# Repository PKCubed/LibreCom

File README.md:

# LibreCom
**An Open-Source, Long-Range, Sub-GHz Digital Intercom System**

Welcome to the **LibreCom** repository. This project aims to build a fully open-source, digital wireless intercom system designed for live event production, theater crews, and other communication applications.

By combining the wall-penetrating power of **Sub-GHz radio**, high quality low bandwidth **OPUS audio compression**, and a custom **TDMA (Time-Division Multiple Access)** protocol, this system supports multiple simultaneous talkers and infinite listeners over distances that standard 2.4GHz/Wi-Fi systems cannot reach.

This project wont be quite as feature rich as the top-of-the-line communication systems on the market, but with it's incredibly low price and open-source nature, we hope for it to reach into the live event production world.

## Sponsored by PCBWay!

<p align="center">
  
</p>

A huge thank you to **[PCBWay](https://www.pcbway.com/)** for sponsoring LibreCom!

PCBWay is providing PCB fabrication and assembly for our prototype hardware. Hardware projects like this one need many board revisions to get RF layout, audio grounding, and power design right. Their support lets us iterate quickly without the cost of each spin slowing development down.

We're currently just about to order our first PCB revision, and once we get it back we'll upload pictures and share our experience here.

If you're building your own LibreCom hardware, the Gerber files in the production folders are ready to upload directly to PCBWay. They also offer **PCB assembly**, **stencils**, **3D printing**, and **CNC machining**, which are useful if you want a finished enclosure for your belt pack too.

**[Order LibreCom boards from PCBWay](https://www.pcbway.com/)**

---

## System Feature Goals

### Overall System
* **Low Latency:** Latency should be low enough such that conversations can be made quickly.
* **Flexibility:** Each belt pack should support any standard TRRS headset. The hub should allow analog connections as well to interface with other systems.

### The Belt Packs (End-User Nodes)
The belt packs are designed to be cheap, rugged, and feature-rich for live-event professionals.
* **Standard Headset Support:** Uses universal TRRS (3.5mm) headsets (CTIA).
* **Local IEM Mixing:** Features an external stereo input jack. You can plug in an In-Ear Monitor (IEM) pack or other device, and the belt pack will mix this audio locally with the coms feed fed into the headset.
* **Spatial Panning:** Comm audio can be software-panned entirely to the Left or Right ear, allowing users to separate crew chatter from program audio.
* **Audio Ducking** User's can configure the belt packs to duck other audio making way for priority talkers.
* **Physical Controls:**
  * Volume Knob
  * Push-To-Talk (PTT) Button
  * Push-To-Mute Button (Configurable to mute either the mic, the comm feed, or the local IEM feed)
* **VOX Support:** Voice Operated Exchange for hands-free operation without needing the PTT button.
* **Multiple Talk Groups:** More than one conversation space for separating teams like video and stage crews while keeping the ability to broadcast to specific or all talk groups.

### The Base Station (Central Matrix)
For structured events (theater, concerts), the system relies on a Base Station to act as the TDMA master clock and audio routing matrix.
* **Program Audio Injection:** Jacks to input external audio (like a Front-of-House stage mix) to be broadcast to all belt packs.
* **Hardware Outputs:** Multiple physical audio outputs on the base station that can be routed in software (e.g., routing "Talk Group A" to Output 1, and "Talk Group B" to Output 2 for the stage manager's console).
* **Web UI Management:** The base station hosts a local web server interface. Stage managers can connect via phone/laptop to change user volumes, assign talk groups, configure priorities, and monitor battery levels.

### Decentralized "Mesh" Mode (stretch goal)
No base station? No problem. The belt packs can be configured to operate in a completely decentralized mode. Perfect for outdoor sports (skiing, hiking, airsoft) where a group of friends can communicate directly point-to-point like highly advanced digital walkie-talkies.

---

## Hardware Architecture

The hardware is designed to decouple the heavy digital signal processing from the strict timing requirements of the radio link.

* **Belt Pack Main Processor (MCU):** ESP32-S3
* **Radio Transceiver:** SX1262
* **Audio Frontend:** I2S Audio DAC and ADC IC with amplification for both headphones and for a microphone.
* **The Hub:** Raspberry Pi Hat with custom hat including SX1262, I2S ADCs and DACs for physical audio IO, and some kind of physical user interface for quick adjustments to the system's configuration

---

## Licensing

To ensure this project remains open and beneficial to the community while allowing for commercial manufacturing:

* **Software / Firmware:** Licensed under the **GNU GPLv3**.
* **Hardware / PCBs:** Licensed under the **CERN-OHL-S** (Strongly Reciprocal). 

You are free to build, use, and sell this hardware. However, if you modify the circuit board designs or the firmware and distribute the resulting product, you must share your modifications back with the community under the same open licenses.

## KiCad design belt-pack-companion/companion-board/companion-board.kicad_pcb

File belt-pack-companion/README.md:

# ESP32 Pin Connections
| ESP32 Pin | Connection | | ESP32 Pin | Connection |
| --- | --- |-| --- | --- |
| 7 |  | | 19 | Button 1 |
| 6 | I2C SCL | | 20 | Button 2 |
| 5 | I2C SDA | | 21 |  |
| 4 | I2S SPK Data | | 26 |  |
| 3 |  | | 48 | SD DAT3 |
| 2 | I2S WCLK | | 47 | SD DAT2 |
| 1 |  | | 33 | CODEC Reset |
| 38 | I2S BCLK | | 34 | I2S MIC Data |
| 39 | SD CLK | | 35 |  |
| 40 | SD CMD  | | 36 |  |
| 41 | SD DAT0 | | 0 |  |
| 42 | SD DAT1 | |  |  |
| 45 | Red LED | | 43 |  |
| 46 | Green LED | | 44 |  |
| 37 |  | |  |  |

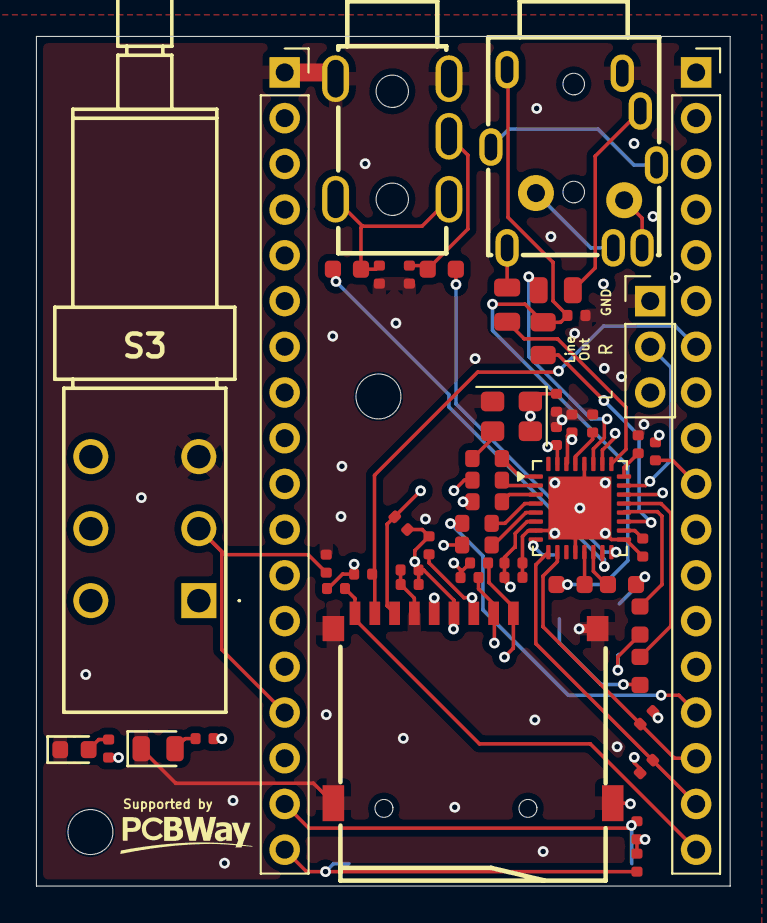
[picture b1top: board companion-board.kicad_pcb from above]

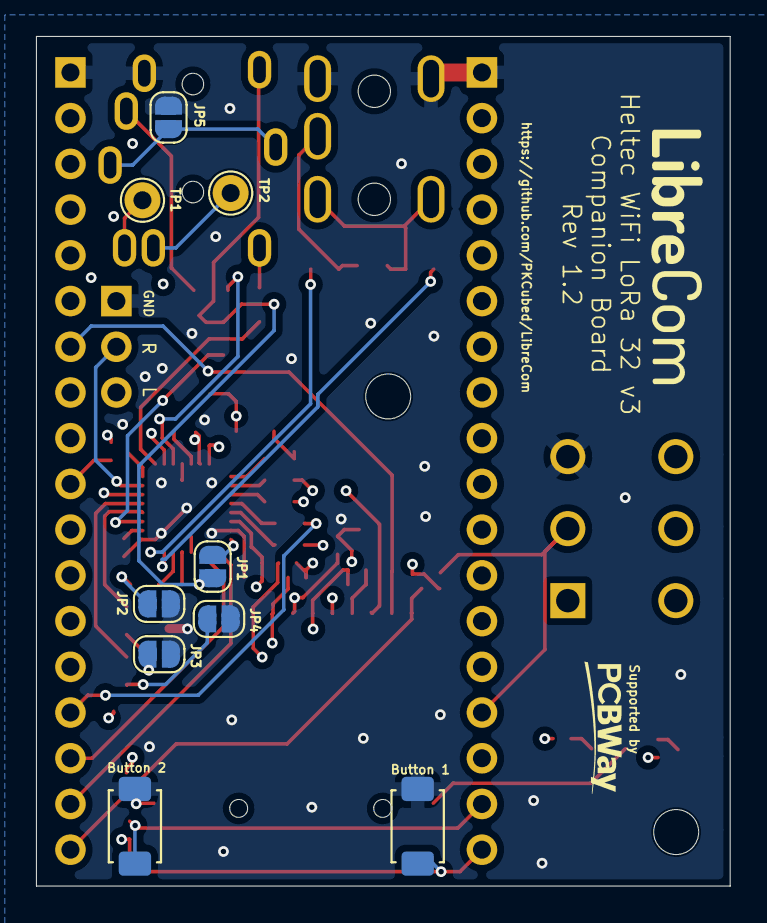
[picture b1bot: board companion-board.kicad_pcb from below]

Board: 4 copper layers, 38.5 x 47.2 mm, 63 parts (9 on the bottom side), 56 nets.

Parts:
C1, C4, C8, C9, C16: 10uF; C_0402
C2: 1uF; C_0402
C3: 1nF; C_0402
C5, C6: 47uF; C_0805
C7, C10, C11, C12, C13, C14: 100nF; C_0603
C15, C17: 100nF; C_0402
CARD1: TF-SMD_TF-01A
D1: Red; D_0603
D4: Green; D_0805
H1, H2: MountingHole; MountingHole_2.5mm
J1, J2: Conn_01x18_Socket; PinSocket_1x18_P2.54mm_Vertical
J3: AUDIO-TH_PJ313D
J4: Conn_01x03_Pin; PinHeader_1x03_P2.54mm_Vertical
JP1, JP2, JP3, JP4, JP5: SolderJumper_2_Open; SolderJumper-2_P1.3mm_Open_RoundedPad1.0x1.5mm
R1, R2, R3, R4: 27Ω; R_0603
R5: 10Ω; R_0603
R6: 2.7kΩ; R_0805
R7, R14: 4.7kΩ; R_0402
R8: 33Ω; R_0402
R9: 330Ω; R_0402
R13, R15, R16, R23, R24, R27, R28, R29, R30, R31: 10kΩ; R_0402
R18: 470Ω; R_0402
R26, R32, R33: 100kΩ; R_0402
S1, S2: Tactile Button, 160gf; SW_TS-1088-AR02016
S3: MPBS-22H01-F14; MPBS22H01F14
TP1, TP2: TestPoint; TestPoint_THTPad_D2.0mm_Drill1.0mm
U1: TLV320AIC3204; VQFN-32-1EP_5x5mm_P0.5mm_EP3.5x3.5mm
U2: AUDIO-TH_PJ-3401
X1: YC24.576MUBCE2O; Oscillator_SMD_Abracon_ASE-4Pin_3.2x2.5mm

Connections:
+3.3V: C1.1, C2.1, C3.1, C15.1, C16.1, C17.1, CARD1.4 (VDD), J1.2, J1.3, R7.2, R14.1, R15.2, R16.2, R23.1, R27.1, R28.1, R29.1, R30.1, R31.1, S3.1 (NO_1), U1.6 (IOVDD), U1.26 (LDOIN/HPVDD), U1.30 (LDO_SELECT), X1.1 (EN), X1.4 (Vdd)
Button_1: J2.18, R15.1, S2.1 (A)
Button_2: J2.17, R16.1, S1.1 (A)
Button_PTT: J2.15, R24.1, S3.2 (COM_1)
CODEC_RESET: J2.12, R13.2, U1.31 (~RESET)
GND: C1.2, C2.2, C3.2, C4.2, C8.2, C9.2, C15.2, C16.2, C17.2, CARD1.6 (VSS), CARD1.10 (GND), CARD1.11 (GND), CARD1.12 (GND), CARD1.13 (GND), D1.1, D4.1, J1.1, J2.1, J3.2, J4.1, JP2.2 (B), JP3.2 (B), JP4.2 (B), JP5.1 (A), R13.1, R24.2, R26.2, R32.2, R33.2, S1.2 (B), S2.2 (B), S3.3 (NC_1), U1.7 (IOVSS), U1.12 (SPI_SELECT), U1.17 (AVSS), U1.28 (DVSS), U1.33 (EP), U2.1 (GND/MIC), X1.2 (GND)
HS_Left: C5.2, U2.3 (L)
HS_Right: C6.2, U2.2 (R)
I^{2}C_SCL: J1.17, R7.1, U1.9 (SCL/~SS)
I^{2}C_SDA: J1.16, R14.2, U1.10 (SDA/MOSI)
I^{2}S_BCLK: J1.11, R4.1
I^{2}S_MCLK: R5.2, U1.1 (MCLK)
I^{2}S_MIC_DATA: J2.11, R2.1
I^{2}S_SPK_DATA: J1.15, R1.1
I^{2}S_WCLK: J1.13, R3.1
LED_Green: J1.5, R9.1
LED_Red: J1.6, R18.1
LINE_IN_L: C10.2, J3.4, R32.1
LINE_IN_R: C11.2, J3.3, R33.1
Line_Out_Left: J4.3, U1.22 (LOL)
Line_Out_Right: J4.2, U1.23 (LOR)
MIC: C7.2, JP1.1 (A), R6.2, R26.1, U2.4 (GND/MIC)
unnamed: D1.2, R18.2
unnamed: D4.2, R9.2
unnamed: J1.10, R8.2
unnamed: JP1.2 (B), U1.8 (SCLK/MFP3)
unnamed: C12.2, JP2.1 (A)
unnamed: C13.2, JP3.1 (A)
unnamed: C14.2, JP4.1 (A)
unnamed: JP5.2 (B), U2.7 (SHELL), U2.8 (SHELL)
unnamed: TP1.1 (1_1), U2.6
unnamed: TP2.1 (1_1), U2.5
unnamed: C8.1, U1.24 (AVDD)
unnamed: R3.2, U1.2 (BCLK)
unnamed: R1.2, U1.4 (DIN/MFP1)
unnamed: R2.2, U1.5 (DOUT/MFP2)
unnamed: C9.1, U1.29 (DVDD)
unnamed: C5.1, U1.25 (HPL)
unnamed: C6.1, U1.27 (HPR)
unnamed: C7.1, U1.13 (IN1_L)
unnamed: C12.1, U1.14 (IN1_R)
unnamed: C10.1, U1.15 (IN2_L)
unnamed: C11.1, U1.16 (IN2_R)
unnamed: C13.1, U1.20 (IN3_L)
unnamed: C14.1, U1.21 (IN3_R)
unnamed: R6.1, U1.19 (MICBIAS)
unnamed: C4.1, U1.18 (REF)
unnamed: R4.2, U1.3 (WCLK)
unnamed: R5.1, X1.3 (OUT)
SD_CLK: CARD1.5 (CLK(SCLK)), R8.1
SD_CMD: CARD1.3 (CMD(DI)), J1.9, R30.2
SD_DAT0: CARD1.7 (DAT0(D0)), J1.8, R29.2
SD_DAT1: CARD1.8 (DAT1(RSV)), J1.7, R28.2
SD_DAT2: CARD1.1 (DAT2(RSV)), J2.13, R27.2
SD_DAT3: CARD1.2 (CDDAT3(CS)), J2.14, R31.2
SD_DETECT: CARD1.9 (CD), J1.18, R23.2

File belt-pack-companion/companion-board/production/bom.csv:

Designator,Footprint,Quantity,Value,LCSC Part #
"C1, C16, C4, C8, C9",C_0402,5,10uF,C15525
"C10, C11, C12, C13, C14, C7",C_0603,6,100nF,C14663
"C15, C17",C_0402,2,100nF,C1525
C2,C_0402,1,1uF,C52923
C3,C_0402,1,1nF,C1523
"C5, C6",C_0805,2,47uF,C16780
CARD1,TF-SMD_TF-01A,1,~,C91145
D1,D_0603,1,Red,C2286
D4,D_0805,1,Green,C2297
"J1, J2",PinSocket_1x18_P2.54mm_Vertical,2,Conn_01x18_Socket,
J3,AUDIO-TH_PJ313D,1,~,C18167
J4,PinHeader_1x03_P2.54mm_Vertical,1,Conn_01x03_Pin,
"R1, R2, R3, R4",R_0603,4,27Ω,C25190
"R13, R15, R16, R23, R24, R27, R28, R29, R30, R31",R_0402,10,10kΩ,C25744
"R14, R7",R_0402,2,4.7kΩ,C25900
R18,R_0402,1,470Ω,C25117
"R26, R32, R33",R_0402,3,100kΩ,C25741
R5,R_0603,1,10Ω,C22859
R6,R_0805,1,2.7kΩ,C17530
R8,R_0402,1,33Ω,C25105
R9,R_0402,1,330Ω,C25104
"TP1, TP2",TestPoint_THTPad_D2.0mm_Drill1.0mm,2,TestPoint,
U1,VQFN-32-1EP_5x5mm_P0.5mm_EP3.5x3.5mm,1,TLV320AIC3204,C24109
U2,AUDIO-TH_PJ-3401,1,~,C5146693
X1,Oscillator_SMD_Abracon_ASE-4Pin_3.2x2.5mm,1,YC24.576MUBCE2O,C52204801

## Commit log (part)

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2026-04-21 Revise README with detailed project overview
    Expanded project description and added system features, hardware architecture, project roadmap, and licensing information.
2026-04-21 Fix indentation for Physical Controls section
    Added indentation for the 'Volume Knob' item under Physical Controls.
2026-05-12 Revise system features and hardware specifications
    Updated system features section for clarity and detail, including changes to headset support, IEM mixing, spatial panning, and hardware components.
2026-05-14 Uploaded testing files
2026-05-14 rp2350 test somewhat functional
    The codec 2 implementation is translating the fundamental frequency, but speech is still unintelligible.
2026-05-14 DAC PIO code fixed
2026-05-14 Implemented codec 2 bypass test
    Using a uart line as an I2S passthrough works perfectly! This is a great test of the hardware, all that needs to be implemented is the codec 2 compression.

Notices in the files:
README.md:
License: GPL v3
License: CERN-OHL-S
